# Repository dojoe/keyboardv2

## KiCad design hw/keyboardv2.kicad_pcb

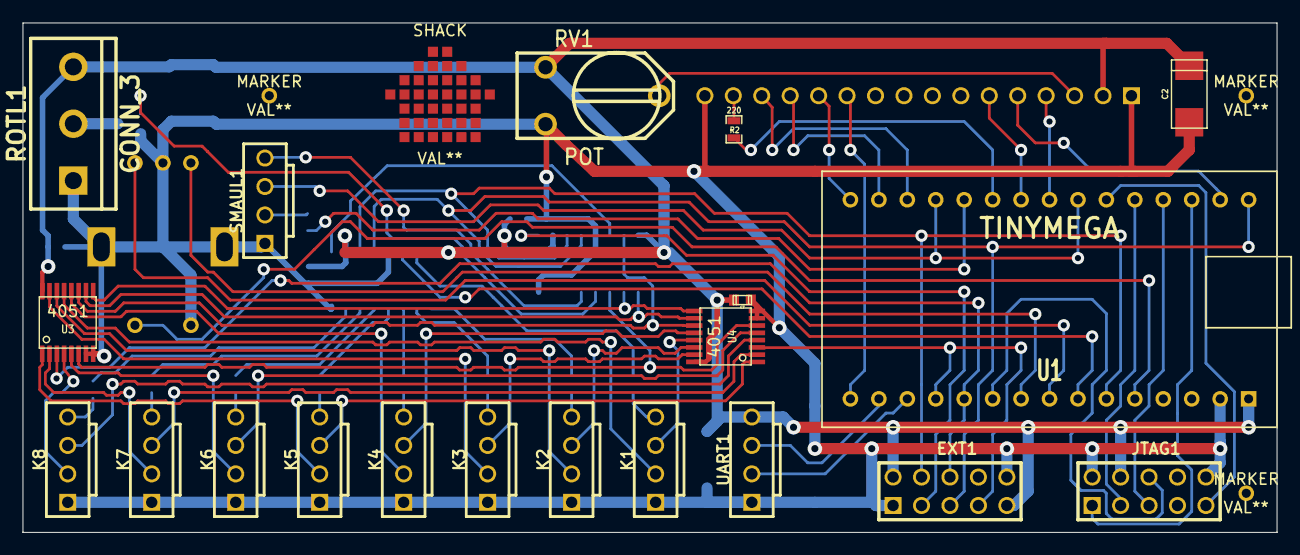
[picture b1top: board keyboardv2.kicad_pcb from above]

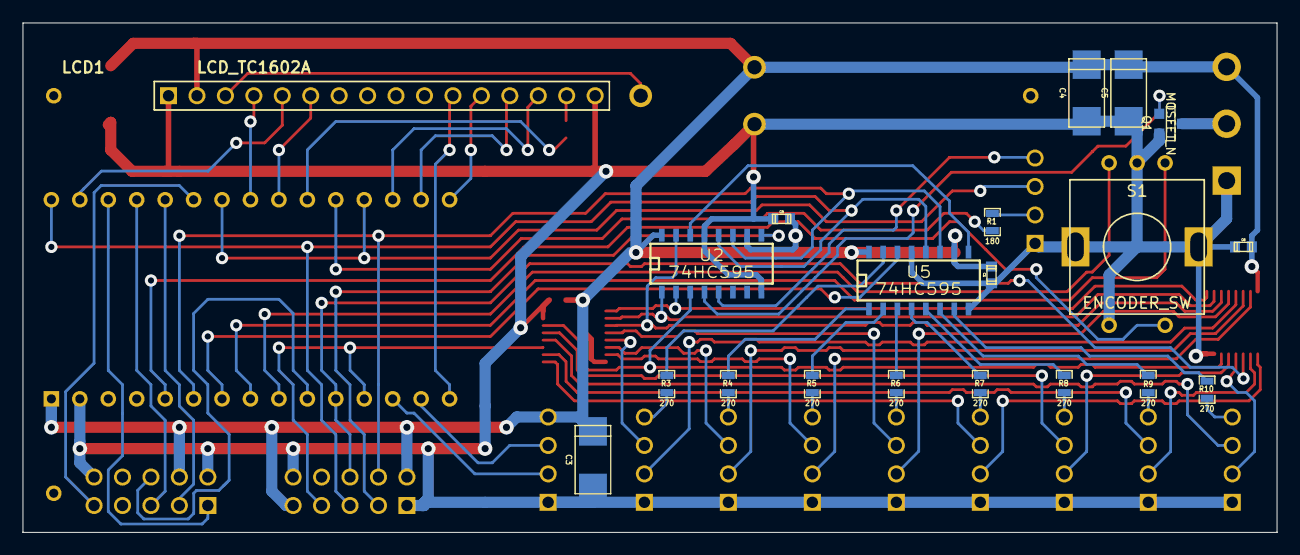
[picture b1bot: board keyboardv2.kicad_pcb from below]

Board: 2 copper layers, 112.0 x 45.5 mm, 44 parts (20 on the bottom side), 71 nets.

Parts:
C1, C6, C7, C8: 100n; c_0603
C2, C3, C4, C5: 10u; c_tant_C
EXT1: CONN_5X2; PIN_ARRAY_5x2_BPAD
JTAG1: CONN_5X2; PIN_ARRAY_5x2_BPAD
K1, K2, K3, K4, K5, K6, K7, K8: CONN_4; PIN_ARRAY_4x1_KEYED_BPAD
LCD1: LCD_TC1602A; pin_array_16x1_BPAD
MARKER: VAL**; MARKER
MARKER#2, MARKER#3: VAL**; MARKER
Q1: MOSFET_N; SOT23GDS
R1: 180; SM0603_Resistor
R2: 220; SM0603_Resistor
R3, R4, R5, R6, R7, R8, R9, R10: 270; SM0603_Resistor
ROTL1: CONN_3; bornier3
RV1: POT; RV2X4
S1: ENCODER_SW; Alps-EC11-Vert
SHACK: VAL**; SHACK
SMAUL1: CONN_4; PIN_ARRAY_4x1_KEYED_BPAD
U1: TINYMEGA; TinyMega
U2, U5: 74HC595; SO16E
U3, U4: 4051; tssop-16
UART1: CONN_4; PIN_ARRAY_4x1_KEYED_BPAD

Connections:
/!RESET: JTAG1.6, U1.10
/BLAULICHT: Q1.G, U2.4
/BLPWR: Q1.D, ROTL1.2
/BUZZER: SMAUL1.4, U2.5
/ENC_A: S1.2, U1.8
/ENC_B: S1.3, U1.9
/ENC_PUSH: S1.4, U1.5
/Key Jacks/!KEY_EN: U2.3, U3.6, U4.6
/Key Jacks/KEY_PWR: EXT1.6, U1.11, U3.3
/Key Jacks/KEY_SCIO: EXT1.7, U1.12, U4.3
/Key Jacks/KEY_SEL0: U2.15, U3.11, U4.11
/Key Jacks/KEY_SEL1: U2.1, U3.10, U4.10
/Key Jacks/KEY_SEL2: U2.2, U3.9, U4.9
/Key Jacks/LED_LATCH: EXT1.5, U1.30, U2.12, U5.12
/Key Jacks/LED_SCK: EXT1.4, U1.6, U2.11, U5.11
/Key Jacks/LED_SIN: U1.7, U5.14
/Key Jacks/LED_SOUT: U2.14, U5.9
/Key Jacks/led0: R3.2, U5.15
/Key Jacks/led1: R4.2, U5.1
/Key Jacks/led2: R5.2, U5.2
/Key Jacks/led3: R6.2, U5.3
/Key Jacks/led4: R7.2, U5.4
/Key Jacks/led5: R8.2, U5.5
/Key Jacks/led6: R9.2, U5.6
/Key Jacks/led7: R10.2, U5.7
/Key Jacks/pwr0: K1.2, U3.13
/Key Jacks/pwr1: K2.2, U3.14
/Key Jacks/pwr2: K3.2, U3.15
/Key Jacks/pwr3: K4.2, U3.12
/Key Jacks/pwr4: K5.2, U3.1
/Key Jacks/pwr5: K6.2, U3.5
/Key Jacks/pwr6: K7.2, U3.2
/Key Jacks/pwr7: K8.2, U3.4
/Key Jacks/scio0: K1.3, U4.13
/Key Jacks/scio1: K2.3, U4.14
/Key Jacks/scio2: K3.3, U4.15
/Key Jacks/scio3: K4.3, U4.12
/Key Jacks/scio4: K5.3, U4.1
/Key Jacks/scio5: K6.3, U4.5
/Key Jacks/scio6: K7.3, U4.2
/Key Jacks/scio7: K8.3, U4.4
/LCD_D0: LCD1.11, U1.15
/LCD_D1: LCD1.12, U1.16
/LCD_D2: LCD1.13, U1.17
/LCD_D3: LCD1.14, U1.18
/LCD_E: LCD1.6, U1.22
/LCD_LED: R2.2, U1.21
/LCD_RS: LCD1.4, U1.23
/LCD_RW: LCD1.5, U1.29
/M_RX: U1.13, UART1.2
/M_TX: U1.14, UART1.3
/SMAUL_BTN: SMAUL1.3, U1.19, U1.24
/SMAUL_LED: R1.1, U1.20
/SOUT: EXT1.3, U2.9
/TCK: JTAG1.1, U1.28
/TDI: JTAG1.9, U1.25
/TDO: JTAG1.3, U1.26
/TMS: JTAG1.5, U1.27
GND: C1.2, C2.2, C3.2, C4.2, C5.2, C6.2, C7.2, C8.2, EXT1.1, EXT1.10, JTAG1.2, JTAG1.10, K1.1, K2.1, K3.1, K4.1, K5.1, K6.1, K7.1, K8.1, LCD1.1, LCD1.16, Q1.S, ROTL1.1, RV1.3, S1.1, S1.5, S1.6, SMAUL1.1, U1.2, U2.8, U2.13, U3.7, U3.8, U4.7, U4.8, U5.8, U5.13, UART1.1
unnamed: LCD1.15, R2.1
unnamed: LCD1.3, RV1.2
unnamed: R1.2, SMAUL1.2
unnamed: K8.4, R10.1
unnamed: K1.4, R3.1
unnamed: K2.4, R4.1
unnamed: K3.4, R5.1
unnamed: K4.4, R6.1
unnamed: K5.4, R7.1
unnamed: K6.4, R8.1
unnamed: K7.4, R9.1
VCC: C1.1, C2.1, C3.1, C4.1, C5.1, C6.1, C7.1, C8.1, EXT1.2, EXT1.9, JTAG1.4, LCD1.2, ROTL1.3, RV1.1, U1.1, U2.10, U2.16, U3.16, U4.16, U5.10, U5.16, UART1.4

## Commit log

2013-10-18 Initial firmware commit with USB serial and EEPROM communication
2013-10-20 Key detection
2013-11-01 Add LCD driver (courtesy of danni) and still-haxxy rotary decoder
2013-11-01 Remove debug onewire clock
2013-11-03 Add hardware schematics
2013-11-03 Move input polling to timer interrupt
2013-11-13 Add decaps, make schematic fit for PCB, start PCB
2013-11-16 Change LED pin order, complete routing of key jacks
2013-11-16 Routed all signals, only VDD/GND remaining
2013-11-16 All connections routed! \o/
2013-11-17 Yeah, so I had the board reversed -.- Once more with feeling.
2013-11-17 Board complete. Again.
2013-12-03 Assign LED resistor values, change some labels for readability
2013-12-03 Started bringup; some inputs, LCD, PWM LEDs and shift regs working
2013-12-14 Bring up multiplexers, UNI/O and EEPROM read, simplify input code
2014-01-12 Commit firmware TODO with some design thoughts
2014-01-12 Extract panel functions into own module, switch to latest LUFA
2014-01-12 Forgot to commit hw.h
2014-01-24 Implement beeper driver
2014-01-26 LCD backlight, Smaul LED, key LEDs
2014-02-08 Genericize events, add timer event, add key management state machine
2014-02-08 Remove some debug code from last commit
2014-02-09 Fix sporadic onewire failures due to irregular interrupt timing causing onewire clock jitter
2014-02-16 Move USB code out of main.c
2014-02-22 Command parser, configuration, and some commands
2014-03-02 Adapt makefile for BatchISP support, add BatchISP script
2014-03-02 Add key programming via serial console, move some strings into PROGMEM
2014-03-02 Move some more const data into flash
2014-03-03 Add key DB commands for feature complete command module
2014-03-03 Put object files into subdirectory
2014-03-15 added tests for button up
2014-03-15 unified tests for encoder in menu, added start of a test that checks if the menu can perform an action and then shuts down
2014-03-15 added example test for menu
2014-03-15 added caps for time selection at 99 minutes and 1 minutes
2014-03-15 weiter am menu
2014-03-15 selection of time works for now
2014-03-15 menu will be terminated when timeout occurs.
2014-03-15 decommented code
2014-03-15 wenn man tasten drückt, refreshed sich der menu timer
2014-03-15 added test for menu timer, code doesn't work yet
2014-03-15 ablaufen schluessentimer
2014-03-15 beeps when timer runs out.
2014-03-15 i was stupid
2014-03-15 weiter gehackt
2014-03-15 rename schluesseltimer --> keytimer - for more english inside the repo
2014-03-15 rename schluesseltimer --> keytimer - for more english inside the repo - and i failed.
2014-03-15 smaul will mute the first timer and reset it to 5 minutes.
2014-03-15 pizza timer can be stopped using the menu
2014-03-15 changed the drehencoder's direction
2014-03-15 unfortunately different things were implemented with this commit: - changed the rotation order for the rotary knob: clockwise to increment, counterclockwise to decrement - changed lcd timeout to 30 s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
2014-03-15 prints --- when timer is inactive
2014-03-15 LCD convenience layer, takes care of scrolling
2014-03-15 Make UI code ready for main loop, integrate into main(), use new LCD wrapper
2014-03-15 Only update LCD on state transitions
2014-03-15 Add UI states like key search or bootloader; work in progress
2014-03-16 smaul button will pulse when keys / timers are overdue
2014-03-16 menu tests have been discarded.
2014-03-16 fixed a typo
2014-03-16 missing keys are detected and trigger alerts
2014-03-17 wrote detection code for cases where we have a key that belongs to another keyboard
2014-03-29 timer selection ui does not turnarount to 99 minutes when going to a number smaller than 1 minute
2014-03-29 Coding style fixes, refactoring and fixes around key timer
2014-03-29 Debounce key states
2014-03-29 Only start handling key change events when all key slots have a known state
2014-03-29 Fix key missing message being updated too often
2014-03-29 Various fixes, ohai and obai messages
2014-03-30 Change timeout selection unit to minutes
2014-03-30 Refactor piza timer handling, fix several UI bugs related to key insertion and removal
2014-03-30 Add key error handling, move error state management into UI code
2014-03-30 Pulse Smaul button LED while keys are missing
2014-03-30 Config command to disable beeper
2014-03-30 Separate scrolling and LCD update, adapt scrolling to slow LCD
2014-03-30 Overengineer Smaul LED pulsing, separate from UI repainting
2014-03-31 Start Smaul LED effects in defined state
2014-03-31 Some timer related fixes
2014-03-31 Use sign checks for timers
2014-03-31 Move LUT generation code into separate file
2014-03-31 Don't apply selected time on menu timeout, merge menu and selection timeout
2014-04-02 On key alarm, sync smaul LED to beeper
2014-04-02 Change timeout selection message to something more descriptive
2014-04-02 Different maximum text lengths for LCD line 1 and 2
2014-04-02 List missing keys during idle
2014-04-02 Make sure smaul pulsing is not reset during UI state changes
2014-04-03 Add support for rotating light, adhere to key flags
2014-04-03 Serial: Add reminder to reset after config change, add reset command
2014-04-03 Small text changes
2014-04-03 Remove bootloader menu item in non-debug builds
2014-04-03 Add firmware version
2014-04-17 Make shiftreg value updates atomic, properly abort SPI transmission when restarting (possibly fixes issue #1)
2014-07-21 Add test mode to manually enable/power/scan individual slots
